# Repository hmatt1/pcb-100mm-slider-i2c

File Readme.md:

# pcb-100mm-slider-i2c

Preface:

> Hi everyone!
>
> This blog post explains how to make a PCB from scratch.
>
> It is pretty detailed on the technical side, with a goal of demistifying a lot about hardware.
>
> It also talks about my experience working with [PCBWay](https://www.pcbway.com/), who was kind enough to fund this project. They were supportive and gave me lots of freedom too. PCBWay was a great
> way to get my custom PCB design turned into reality, so I included a lot of detail on how that is done to hopefully help anyone who is new to PCB design.
>
> Thanks for reading and I hope you enjoy :) 

----

# Building a slider PCB from scratch

This [slider](https://www.adafruit.com/product/5295) from Adafruit is cool, but it has a problem. It is too small.

It only has 65mm of travel distance for the slider movement.

Fortunately, it was easy to find a longer slider.

This is the PTB0143-2010BPA103, in Bourn's PTB Series. It is a Low Profile Slide Potentiometer.

It has a whopping 100mm of travel! Here are some other specs:

Resistance: 10 kOhms
Tolerance: 20%	
Taper: Linear
Life: 15,000 Cycles

15k cycles is pretty nice! I've already used 3 of them. 14,997 until it starts to wear out! Wahoo!

It's an awesome part, but we still have a problem. It's not attached to a PCB, so it doesn't have an I2C interface to actually start working with it.

So obviously, I'm going to have to build that part myself. Fortunately, we have a great path forward.

After my [last blog post](https://hackaday.io/project/205240-usb-to-i2c-demo), [Aran](https://x.com/pcbway_aran) from [PCBWay](https://www.pcbway.com/) messaged me to see if [PCBWay](https://www.pcbway.com/) could sponsor my next project. 

**This was a really delightful surprise!**

I never expected to get that kind of recognition for my [last project](https://hackaday.io/project/205240-usb-to-i2c-demo). Also, I do often see [PCBWay](https://www.pcbway.com/) sponsoring YouTubers that I like, so I was excited that they reached out.

There's a lot to explain before we can send the design to PCBWay.

The first thing to cover is how a potentiometer works.

And to understand that, let's review a simple voltage divider.

The formula is:

```
Vout = Vin*R2/(R1+R2) 
```

So it lets you split voltages over resistors in series.

Here is an example with some voltage numbers.

A slide potentiometer is basically just a variable resistor. So it is a resistor that goes between 0 and 10k ohms as you slide it.

They even show circuit diagrams like these straight in the [Bourns slider datasheet.](https://www.bourns.com/docs/Product-Datasheets/PTB.pdf)

I drew this diagram to help compare.

In the above image, the two resistors would always add up to 10k in total. I just didn't have a good way to represent that in the drawing.

Now that we understand the voltage divider, the next step is to add a capacitor between the wiper and ground to filter out noise.

And I'm sure you're wondering now, what is the other 10k resistor doing in parallel with the circuit?

It's a long story and I'm not sure I even got it right.

First, it's nice to have a resistor in series with a slide pot, because when the wiper is all the way at one end, the resistance is 0 and it's connected to power, so there would be nothing limiting current in the case of a short due to a mistake in the circuit. It probably only needs to be 1k instead of 10k in that case.

It would have been a nice idea to add an optional jumper to bypass that resistor. But now that I think about it, I could pry it off the board and solder the pads together. Yeah, that would work fine if I want to experiment without it!

Second, which is also the main reason it's useful, is being able to use the slide pot as a rheostat instead of a voltage divider. To create a rheostat, you short the wiper to pin 3 of the slide pot. I didn't really find great explanations of this, and ended up getting confused and forgot to add a trace with a jumper to be able to try it in my circuit.

More importantly, I vibe coded this beautiful web demo to illustrate the difference (works better on desktop). Not 100% sure if the numbers it shows are right, but it's a good illustration of how the current flows.

----- DEMO HERE!!!! TODO ------

Looking back, it would have been really great to make this easier to switch between these two configurations on the final circuit! A good lesson learned.

So now that we understand how the slide potentiometer works, what do we do with it?

The answer is simple. We connect AIN0 to an ADC (Analog to Digital converter).

There's tons to choose from, but I decided to use the ADS112C04 from Texas Instruments.

Link: https://www.ti.com/product/ADS112C04

The important part was these specs:

| Parameter | Value |
|---|---|
| Resolution (Bits) | 16 |
| Sample rate (max) (ksps) | 2 |
| Interface type | I2C |
|Digital supply (min) (V) | 2.3 |
|Digital supply (max) (V) |	5.5 |

This means we can have 2,000 readings per second, which is .5ms response time to the slider moving.

I2C is a super convenient interface for connecting to the chip.

3.3V power fits comfortably in the digital voltage range for the chip.

And finally, the resolution of 16 bit readings is completely overkill. Which is exactly what I wanted!

This basically means the max value from the ADC would be 65,535. 

Remember, the slider is 100mm long.

So in a perfect world, that means if you move the slider 0.00152590219 millimeters, that would equate to changing the digital value by 1.

The real world has a lot more noise obviously.

**I love the idea that moving the slider less than .01mm would be picked up by your computer in less than 1ms.**

Now we have our chip, we need to hook it up to the rest of the circuit:

The analog inputs are pretty easy to connect. AIN0 will go to the wiper of the slide pot, and the rest we just tie to ground. We aren't going to both with AIN2 and AIN3 in this design, and we will just measure the voltage between AIN0 and AIN1.

Next we have some data lines.

which will connect to the socket.

The datasheet said these should be connect to power with 1k pull-up resistors. And a capacitor was added between power and ground to help with filtering noise.

I also set up some jumpers to be able to configure the I2C address of the board.

So in the full schematic, I included these tips I found in my research.

> PCB Habits for 2-layer boards:
>
> - Use 6 mil wide signal trace, 20 mil wide power traces and 13 mil drilled diameter
> - Route components, signals and power paths on layer 1 and a ground plane on layer 2
> - Adjust components for less congested routing and space signal traces far apart
> - When you need to route a cross-under on the bottom layer, make it short. When you can't make it short, add a return strap over it
> - Place decoupling capacitors as close to the power pin of the IC and with as low a loop inductance as practical
> - Use the largest size capacitor in the smallest body with a voltage rating at least 2x the intended rail application. This is usually a 22 uF MLCC capacitor.
> - On all connectors, try to allocate one return for each digital signal, if possible

And here is everything all put together!

The next thing we need to do is pick out the actually parts we want to use to mark the board. That means picking out exactly which capacitor, which resistor, etc.

I found that [partsbox](https://partsbox.com/) is free and is pretty useful to document the list of parts.

Pretty much when I was looking for parts, I would dig through Digikey and Mouser to filter and see what parts are popular for the category.

But I also really wanted to use some super tiny capacitors on the PCB.
They are better for causing less interference in the circuit, and letting you have shorter distance between components. Also, TI specifically recommended ceramic capacitors to use with the ADC.

I found GRM1555C1E103GE01D from Murata, which is a  0.01uF, surface mount, Multilayer Ceramic Capactior. Specifically, it uses the 0402 footprint, which is about 1mm square.

It's actually amazing that [PCBWay](https://www.pcbway.com/) will solder these tiny capacitors perfectly for you. So I can use them freely on my board, and I don't have to deal with soldering them by hand.

The next part is laying out the PCB with KICAD. I can't remember if I used an AI summary or found a blog post or what for these layout guidelines, or I might have just pieces bullet points together from different sources. But it definitely help me along the way!

> **Layout Guidelines**
>
> Employing best design practices is recommended when laying out a printed-circuit board (PCB) for both analog and digital components. This recommendation generally means that the layout separates analog components [such as ADCs, amplifiers, references, digital-to-analog converters (DACs), and analog MUXs] from digital components [such as microcontrollers, complex programmable logic devices (CPLDs), field-programmable gate arrays (FPGAs), radio frequency (RF) transceivers, universal serial bus (USB) transceivers, and switching regulators]. Figure 82 shows an example of good component placement. Although Figure 82 provides a good example of component placement, the best placement for each application is unique to the geometries, components, and PCB fabrication capabilities employed. That is, there is no single layout that is perfect for every design and careful consideration must always be used when designing with any analog component.
>
> The following basic recommendations for layout of the ADS112C04 help achieve the best possible performance of the ADC. A good design can be ruined with a bad circuit layout.
>
> Separate analog and digital signals. To start, partition the board into analog and digital sections where the layout permits. Routing digital lines away from analog lines prevents digital noise from coupling back into analog signals.
>
> The ground plane can be split into an analog plane (AGND) and digital plane (DGND), but is not necessary. Place digital signals over the digital plane, and analog signals over the analog plane. As a final step in the layout, the split between the analog and digital grounds must be connected to together at the ADC.
>
> Fill void areas on signal layers with ground fill.
>
> Provide good ground return paths. Signal return currents flow on the path of least impedance. If the ground plane is cut or has other traces that block the current from flowing right next to the signal trace, another path must be found to return to the source and complete the circuit. If forced into a larger path, the chance that the signal radiates increases. Sensitive signals are more susceptible to EMI interference.
>
> Use bypass capacitors on supplies to reduce high-frequency noise. Do not place vias between bypass capacitors and the active device. Placing the bypass capacitors on the same layer as close to the active device yields the best results.
>
> Consider the resistance and inductance of the routing. Often, traces for the inputs have resistances that react with the input bias current and cause an added error voltage. Reducing the loop area enclosed by the source signal and the return current reduces the inductance in the path. Reducing the inductance reduces the EMI pickup and reduces the high-frequency impedance at the input of the device.
>
> Watch for parasitic thermocouples in the layout. Dissimilar metals going from each analog input to the sensor can create a parasitic thermocouple that can add an offset to the measurement. Differential inputs must be matched for both the inputs going to the measurement source.
>
> Analog inputs with differential connections must have a capacitor placed differentially across the inputs. Best input combinations for differential measurements use adjacent analog input lines (such as AIN0, AIN1 and AIN2, AIN3). The differential capacitors must be of high quality. The best ceramic chip capacitors are C0G (NPO) that have stable properties and low noise characteristics.

and more guidelines specific to our chip:

> **ADS112C04 layout recommendations**
>
> - Separate analog and digital signals. Partition the board into analog and digital sections where the layout permits.
> - The ground plane can be split into AGND and DGND, but is not necessary. Connect the split together at the ADC as a final step.
> - Fill void areas on signal layers with ground fill.
> - Provide good ground return paths. Return current forced into a larger loop increases radiation and EMI susceptibility.
> - Use bypass capacitors on supplies. No vias between the bypass capacitor and the active device, same layer, as close as possible.
> - Consider trace resistance and inductance. Input trace resistance reacts with input bias current and adds an error voltage.
> - Watch for parasitic thermocouples. Match the dissimilar-metal transitions on both differential inputs.
> - Place a differential capacitor across differential inputs. Use adjacent input pairs (AIN0/AIN1, AIN2/AIN3) and C0G (NPO) dielectric.

-----

Anyway, in Kicad, you want to set up each part in the schematic with the symbol properties.

So if I a want to assign C1 to a part, I would open up symbol properties and fill them out.

It looks like this:

This is super important because it will know what footprints to use with which parts of the schematic. And it will let the PCBWay Kicad plugin export the BOM automatically. But more on that later!

So basically, we are tying these things together:

```
Schematic Symbol -> Part Number -> Footprint 
```

So if you look at the menu in Kicad, it should start making sense.

Schematic is the actual diagram. Symbols are symbols on the diagram. Footprints are the geometry that will attach specific parts to the board.

And then PCB Editor is the fun part, where we design the layout of the board itself.

You import the schematic into the PCB Editor, and then draw traces (wires) to connect everything together.

Kicad already knows how your schematic is set up, so it makes sure you can't accidentally connect things that aren't connected in the schematic.

Before you jump into creating the whole PCB design, you need to set up the design rules.

PCBWay has a nice article about Design Rules, and even have the files available to download and import the rules into Kicad.

[PCBWay Design Rules](https://www.pcbway.com/pcb_prototype/PCB_Design_Rule_Check.html)

You'll also want to pay attention to what your manufacturer has available, so you can make sure the rules are correct for that too.

For example, PCBWay lets you select the min spacing and min hole size when [ordering online](https://www.pcbway.com/orderonline.aspx).

So if your min hole size is .3mmm, you don't want to design a PCB with smaller holes  than that. Basically, you want to know all the dimensions of everything in your design.

I think it's a really good idea to pick which manufacturer you want to make your PCB before doing the design. Read through all the options available, so you can ensure your design will meet what they are capable of building.

If you think back to the 1mm capacitor I picked out as a part, not everyone is going to be able to solder that to a board. 

I did look up the [assembly capabilities](https://www.pcbway.com/pcb_prototype/PCB_assembly_Capabilities.html) for PCBWay, to verify this in the documentation:

> we can accept components as small as 01005, 0201,0402.

This means they will deal with my super tiny capacitor! I do not want to try to solder that.

And here is the rendered version:

You can do 3D models of the parts too, but I decided to skip that and trust the footprints. It is a good idea though if you want to take time to verify things will fit together properly in real life.

For exporting files for PCBWay, you can use the [PCBWay Fabrication Toolkit plug-in for Kicad](https://github.com/pcbway/PCBWay-Plug-in-for-Kicad).

You can use when you're in the PCB Editor from the Tools menu.

One click and it will export all the files you need.

Just upload the files to PCBWay and you're good to go.

I'll share what my order looked like here too:

The order includes all the parts and assembly too. I will be getting 5 boards, fully assembled, ready to test out as soon as they arrive at my house! I don't have to mess with any soldering and PCBWay went through the work of sourcing all the different parts. By the way, I did only use [Digikey](https://www.digikey.com/) to find what parts they have in stock. PCBWay ordered parts directly from them for my board, and that was included in the cost of the order.

It was nice that I could just focus on the design.

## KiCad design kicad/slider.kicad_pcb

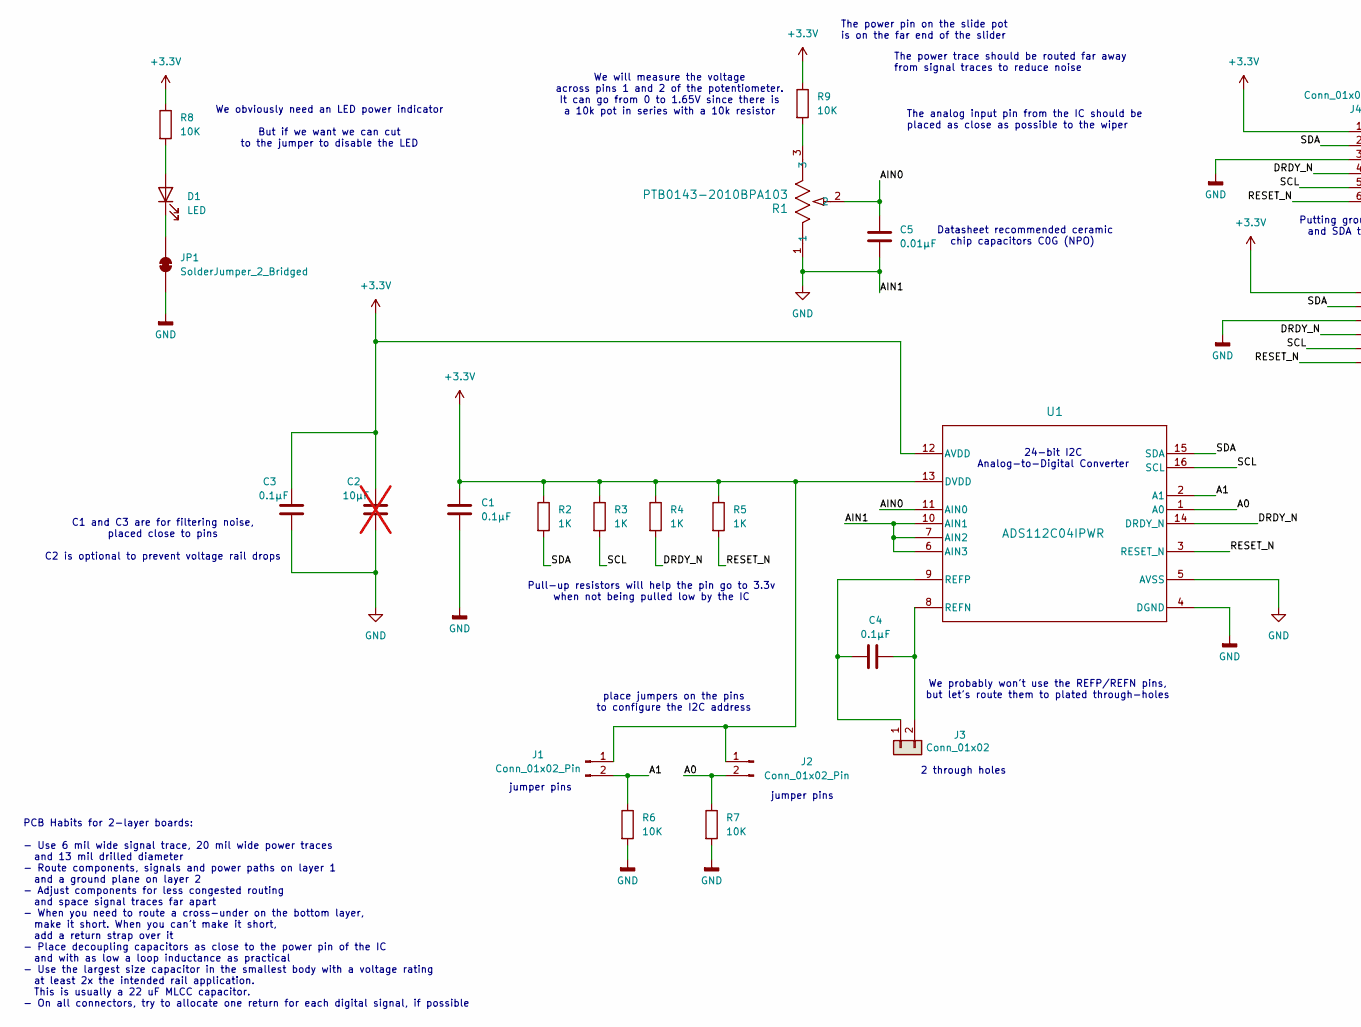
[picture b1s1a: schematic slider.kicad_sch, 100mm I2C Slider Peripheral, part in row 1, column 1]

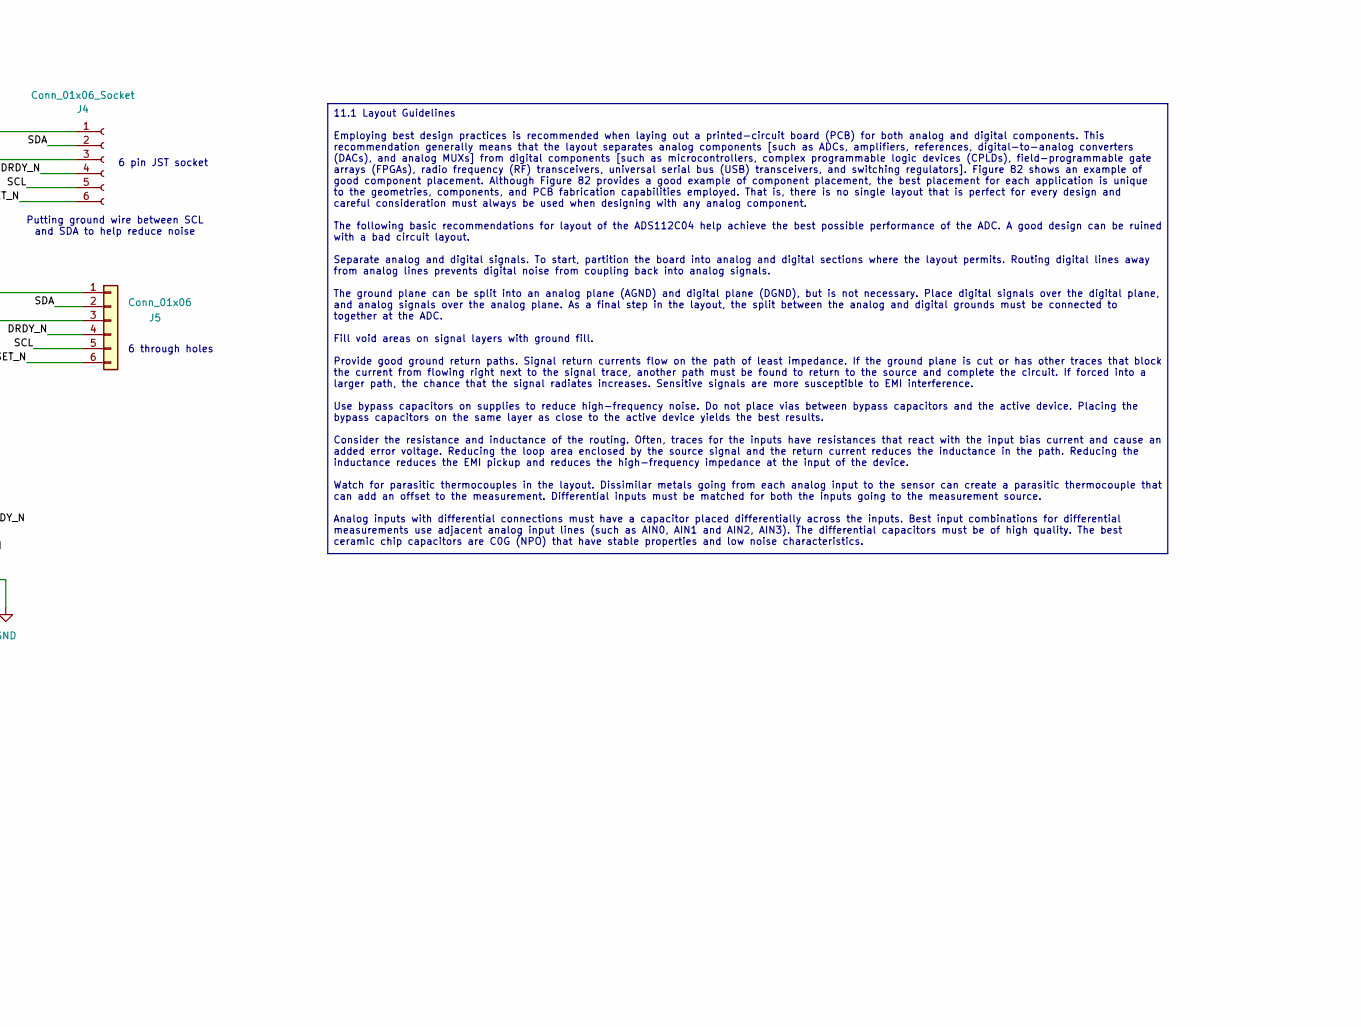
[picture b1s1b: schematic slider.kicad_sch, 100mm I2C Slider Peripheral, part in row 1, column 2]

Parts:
C1, C3, C4: 0.1µF; C_0402_1005Metric_no_silk; MPN GRM155R71C104KA88D
C2: 10µF; C_1210_3225Metric; MPN GCM32ER71E106KA57K; not fitted
C5: 0.01µF; C_0402_1005Metric_no_silk; MPN GRM1555C1E103GE01D
D1: LED; LED_0603_1608Metric; MPN 150060RS75000
J1, J2: Conn_01x02_Pin; 61300211121; MPN 61300211121
J3: Conn_01x02; 61300211121
J4: Conn_01x06_Socket; CONN_S6B-XH-A-1_JST; MPN S6B-XH-A-1
J5: Conn_01x06; CONN06_6130_15P24X2P54_WRE
JP1: SolderJumper_2_Bridged; SolderJumper-2_P1.3mm_Bridged_RoundedPad1.0x1.5mm
R1: PTB0143-2010BPA103; PTB01432010BPB103; MPN PTB0143-2010BPA103
R2, R3, R4, R5: 1K; R_0805_2012Metric; MPN RNCF0805DTE1K00
R6, R7, R8, R9: 10K; R_0805_2012Metric; MPN RNCF0805DTE10K0
U1: ADS112C04IPWR; SOP65P640X120-16N; MPN ADS112C04IPWR

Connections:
+3.3V: C1.1, C2.1, C3.1, J1.1, J2.1, J4.1, J5.1, R2.1, R3.1, R4.1, R5.1, R8.1, R9.1, U1.12 (AVDD), U1.13 (DVDD)
/A0: J2.2, R7.1, U1.1 (A0)
/A1: J1.2, R6.1, U1.2 (A1)
/AIN0: C5.2, R1.2, U1.11 (AIN0)
/DRDY_N: J4.4, J5.4, R4.2, U1.14 (DRDY_N)
/RESET_N: J4.6, J5.6, R5.2, U1.3 (RESET_N)
/SCL: J4.5, J5.5, R3.2, U1.16 (SCL)
/SDA: J4.2, J5.2, R2.2, U1.15 (SDA)
GND: C1.2, C2.2, C3.2, C5.1, J4.3, J5.3, JP1.2 (B), R1.1, R6.2, R7.2, U1.4 (DGND), U1.5 (AVSS), U1.6 (AIN3), U1.7 (AIN2), U1.10 (AIN1)
unnamed: D1.2 (A), R8.2
unnamed: D1.1 (K), JP1.1 (A)
unnamed: C4.1, J3.1, U1.9 (REFP)
unnamed: C4.2, J3.2, U1.8 (REFN)
unnamed: R1.3, R9.2

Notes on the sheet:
C1 and C3 are for filtering noise, placed close to pins C2 is optional to prevent voltage rail drops
Pull-up resistors will help the pin go to 3.3v when not being pulled low by the IC
The analog input pin from the IC should be placed as close as possible to the wiper
place jumpers on the pins to configure the I2C address
2 through holes
Putting ground wire between SCL and SDA to help reduce noise
jumper pins
6 pin JST socket
We probably won't use the REFP/REFN pins, but let's route them to plated through-holes
The power trace should be routed far away from signal traces to reduce noise
We will measure the voltage across pins 1 and 2 of the potentiometer. It can go from 0 to 1.65V since there is a 10k pot in series with a 10k resistor
6 through holes
The power pin on the slide pot is on the far end of the slider
We obviously need an LED power indicator But if we want we can cut to the jumper to disable the LED
PCB Habits for 2-layer boards: - Use 6 mil wide signal trace, 20 mil wide power traces and 13 mil drilled diameter - Route components, signals and power paths on layer 1 and a ground plane on layer 2 - Adjust components for less congested routing and space signal traces far apart - When you need to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
24-bit I2C Analog-to-Digital Converter
Datasheet recommended ceramic chip capacitors C0G (NPO)
11.1 Layout Guidelines Employing best design practices is recommended when laying out a printed-circuit board (PCB) for both analog and digital components. This recommendation generally means that the layout separates analog components [such as ADCs, amplifiers, references, digital-to-analog conver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

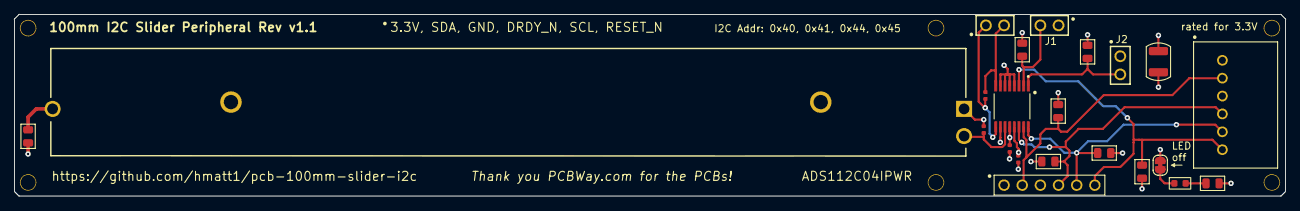
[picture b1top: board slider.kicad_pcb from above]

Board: 4 copper layers, 177.8 x 25.4 mm, 28 parts (0 on the bottom side), 14 nets.

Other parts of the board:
REF1**, REF2**, REF3**, REF4**, REF5**, REF6**: MountingHole_M2_new
